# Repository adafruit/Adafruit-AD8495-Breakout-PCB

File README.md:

# PCB files for Adafruit Analog K-Type Thermocouple Amplifier AD8495 Breakout

Thermocouples are very sensitive, requiring a good amplifier with a cold-compensation reference. We have a couple digital thermocouple amplifiers in the shop already from Maxim. Now we're happy to introduce an excellent analog-output amplifier. This is a very simple sensor to use, and if your microcontroller has analog input capability, you'll be ready to go really fast!

The AD8495 K-type thermocouple amplifier from Analog Devices is so easy to use, we documented the whole thing on the back of the tiny PCB. Power the board with 3-18VDC and measure the output voltage on the OUT pin. You can easily convert the voltage to temperature with the following equation: Temperature = (Vout - 1.25) / 0.005 V. So for example, if the voltage is 1.5VDC, the temperature is (1.5 - 1.25) / 0.005 = 50¡C

Each order comes with a 2 pin terminal block (for connecting to the thermocouple), a fully assembled PCB with the AD8495 + TLVH431 1.25V precision voltage reference, and pin header (to plug into any breadboard or perfboard). [Goes great with our 1m K-type thermocouple (not included)](http://www.adafruit.com/products/270). Not for use with any other kind of thermocouple, K type only!

- Works with any K type thermocouple
- Will not work with any other kind of thermocouple other than K type
- Easy to use analog output
- Temp range with 5V power: -250¡C to +750¡C output (0 to 5VDC) as long as the thermocouple can handle that range
- Temp range with 3.3V power: -250¡C to +410¡C output (0 to 3.3VDC) as long as the thermocouple can handle that range

__Note:__ The terminal blocks included with your product may be blue or black.

## License

Adafruit invests time and resources providing this open source design, 
please support Adafruit and open-source hardware by purchasing 
products from Adafruit!

Designed by Limor Fried/Ladyada for Adafruit Industries.
Creative Commons Attribution, Share-Alike license, check license.txt for more information
All text above must be included in any redistribution

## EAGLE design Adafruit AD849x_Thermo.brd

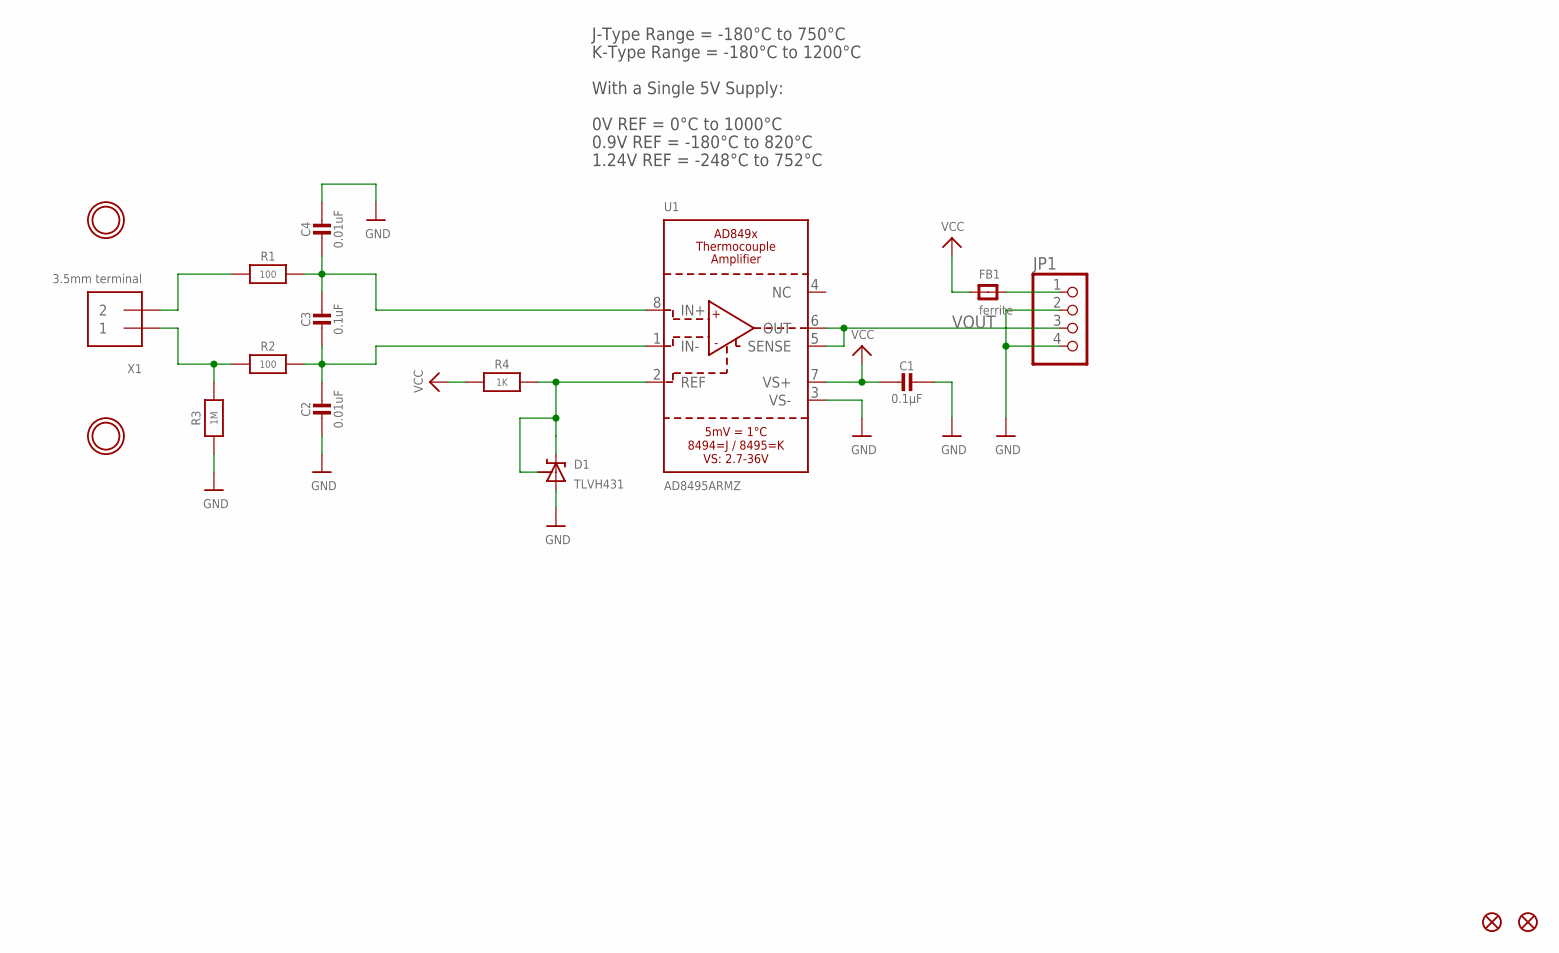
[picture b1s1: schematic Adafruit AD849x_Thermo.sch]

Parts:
C1: 0.1µF; 0805-NO
C2, C4: 0.01uF; 0805-NO
C3: 0.1uF; 0805-NO
D1: TLVH431; SOT23-R
FB1: ferrite; 0805
FID1, FID2: FIDUCIAL""; FIDUCIAL_1MM
JP1: HEADER-1X4ROUND; 1X04_ROUND
R1, R2: 100; 0805-NO
R3: 1M; 0805-NO
R4: 1K; 0805-NO
U1: AD8495ARMZ; MSOP8_0.65MM
U$11, U$12: MOUNTINGHOLE2.5; MOUNTINGHOLE_2.5_PLATED
X1: 3.5mm terminal; TERMBLOCK_1X2-3.5MM

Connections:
GND: C1.1, C2.2, C4.1, D1.3 (A), JP1.2, JP1.4, R3.1, U1.3 (VS-)
IN+: R1.1, X1.2
IN-: R2.1, R3.2, X1.1
unnamed: D1.1 (VREF), D1.2 (C), R4.2, U1.2 (REF)
unnamed: C3.1, C4.2, R1.2, U1.8 (IN+)
unnamed: C2.1, C3.2, R2.2, U1.1 (IN-)
unnamed: FB1.2, JP1.1
VCC: C1.2, FB1.1, R4.1, U1.7 (VS+)
VOUT: JP1.3, U1.5 (SENSE), U1.6 (OUT)

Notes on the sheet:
J-Type Range = -180°C to 750°C
K-Type Range = -180°C to 1200°C
With a Single 5V Supply:
1.24V REF = -248°C to 752°C
0.9V REF = -180°C to 820°C
0V REF = 0°C to 1000°C

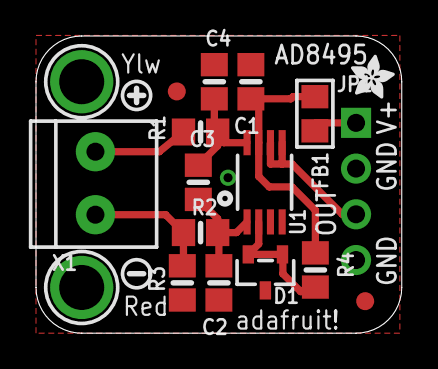
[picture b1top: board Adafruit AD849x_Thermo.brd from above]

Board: 2 copper layers, 20.3 x 16.5 mm, 21 parts (1 on the bottom side), 9 nets.

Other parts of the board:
U$8: SYMBOL_PLUS
U$9: SYMBOL_MINUS
U$10: ADAFRUIT_2.5MM
U$13: ADAFRUIT_3.5MM

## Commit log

2014-06-12 init!
2014-06-12 read me url
2019-05-16 readme + image + license

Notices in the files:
parts and their libraries:
microbuilder: This work is placed in the public domain, and may be freely used for commercial and non-commercial work with the following conditions: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
